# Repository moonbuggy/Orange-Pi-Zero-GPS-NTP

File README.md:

# Orange Pi Zero GPS NTP Server
An Orange Pi Zero with attached GPS, TFT and RTC devices, to create a stratum 1
NTP server.

<p><br/>
<em>Orange Pi Zero GPS NTP Server</em></p>

[moonbuggy/fbgpsclock][moonbuggy/fbgpsclock] is used to interface between the
display and the other devices.

*   [Hardware](#hardware)
    +   [Assembled](#assembled)
    +   [Components](#components)
        -   [Orange Pi Zero](#orange-pi-zero)
        -   [GPS (NEO-M8N)](#gps-neo-m8n)
        -   [TFT display (ST7789V driver)](#tft-display-st7789v-driver)
        -   [Real-time Clock (DS3231)](#real-time-clock-ds3231)
        -   [Power Switch](#power-switch)
    +   [Wiring](#wiring)
        -   [Schematic](#schematic)
        -   [Cable](#cable)
        -   [Power Splitter](#power-splitter)
*   [Software](#software)
    +   [Pre-built OS Image](#pre-built-os-image)
    +   [Manual Configuration](#manual-configuration)
        -   [Armbian](#armbian)
        -   [Status LED](#status-led)
        -   [gpsd](#gpsd)
        -   [chrony](#chrony)
        -   [fbgpsclock](#fbgpsclock)
*   [Links](#links)

## Hardware
### Assembled
<p><br/>
<em>internals</em></p>

<p><br/>
<em>internals (annotated)</em></p>

<p><br/>
<em>top</em></p>

<p><br/>
<em>rear</em></p>

<p><br/>
<em>side</em></p>

There's also [a gallery __(NSFW)__](https://imgur.com/a/yd1e8r0) with some
images from various stages of testing and building.

### Components
#### Orange Pi Zero
Although we're using an Orange Pi Zero (OPiZ) here, the specific single-board
computer used isn't all that important. Any device with UART, SPI, I2C and GPIO
interfaces should work, needing only one of each.

Any device tree overlays in this repository will, however, be specifically for
the OPiZ and would need to be modified for use on other SBCs.

#### GPS (NEO-M8N)
We're using a u-blox NEO-M8N GPS, although any GPS device that _gpsd_ can talk
to should work.

<p><br/>
<em>u-blox NEO-M8N module</em></p>

Soldering a wire to a point between the PPS LED and its current limiting
resistor provides a usable PPS signal on this module.

The GPS is attached through a UART interface (_UART2_), while the
PPS signal is connected separately through a GPIO pin (_pin 15_, _PA03_).

##### Bias tee
A bias tee is installed between the GPS module and the antenna. This allows us
to run the antenna's internal low-noise amplifier (LNA) off the 5V enclosure
supply, rather than the 3.3V that would be provided via the GPS module.Running
the LNA at a higher power should give us better signal.

##### Antenna
There's a lot of antenna options available, it really depends on the use case

A standard panel antenna seems to be more than adequate indoors, inside a
plastic enclosure with the rest of the hardware. Ideally the panel antenna
should have mounting holes so it can be screwed securely to the enclosure,
rather than being taped/glued to a circuit board as may be necessary with
antenna included with the GPS module.

#### TFT display (ST7789V driver)
An LCD screen attached to the OPiZ's SPI bus gives us a way to display
the current time and any other information that may be relevant.

<p><br/>
<em>2.0" SPI TFT</em></p>

A TFT with an ST7789V driver chip and 240x320 pixel resolution has been used in
this case, but a working device tree overlay for a 240x280 pixel display has
also been provided. Other resolutions will work with some minor modifications to
the DT overlay. Using a different driver chip is more complicated.

The exact dimensions of the display don't matter a great deal, it's really only
limited by how much surface area is available on the enclosure to fit a screen.

The TFT display is attached to the SPI1 bus.

#### Real-time Clock (DS3231)
A real-time clock provides accurate time immediately after booting. This is
useful because, coming from a cold start, the GPS module can take a little while
to establish a fix and begin providing time data. Covering this gap with an RTC
means we always have access to a time reference.

The DS3231 is a good option for a cheap and easy I2C RTC module.

<p><br/>
<em>DS3231 RTC module</em></p>

#### Power Switch
A power switch from [moonbuggy/GPIO-power-switch][moonbuggy/GPIO-power-switch]
lets us properly shutdown and cut power to the whole enclosure (including the GPS
module and bias tee).

Making use of the remaining free pins in the cable, we can use the following:

|    signal     | pin | GPIO |
|:-------------:|:---:|:----:|
| GPIO_POWEROFF | 21  | PA16 |
| KEY_POWER     | 12  | PA07 |
| READY_SIGNAL  | 16  | PA19 |

> [!NOTE]
> The _GPIO_SHUTDOWN_ signal requires `CONFIG_POWER_RESET_GPIO` and
> `CONFIG_POWER_RESET_GPIO_RESTART` to be enabled in the kernel, which may not
> be the case for a default OS install.

Due to pin 16 (_PA19_) having an internal pull-up resistor, we'll use the verson
of the power switch with the active low LED so the default LED state at power
up is _not-ready_.

More details are available at [moonbuggy/GPIO-power-switch][moonbuggy/GPIO-power-switch].

### Wiring
#### Schematic
<p><br/>
<em>GPIO wiring</em></p>

#### Cable
The specific pins chosen allow us to make a convenient cable to connect the GPS,
TFT and power control modules while leaving the I2C pins clear for the RTC
module to plug directly in.

<p><br/>
<em>GPS + 2.0" TFT + power control cable schematic</em></p>

> [!NOTE]
> The cable is wired for the specific attached devices. The OPiZ end is static,
> but the other connectors will need to be adjusted to match the pinout of the
> particular TFT and GPS modules in use.

Most of the connectors are standard pin sockets, with a 2x8 socket being used
for the OPiZ end 1x5 and 1x8 sockets on the GPS and TFT modules respectively.
A JST XH2.54 connector is used for the GPIO signals to/from the power control
board.

<p><br/>
<em>GPS + TFT + power control cable</em></p>

The OPiZ end of the cable will attach to GPIO pins 11 to 26. Using a
black wire for the ground connection to OPiZ pin 25 provides a convenient way to
align the connector, regardless of the other wire colours.

#### Power Splitter
<p><br/>
<em>power splitter</em></p>

In an ideal world there'd be enough room in the enclosure to combine this
splitter and the power control circuit on a single PCB, to save a cable run
(although it's not a big deal that they're separate).

Closing the jumper bypasses the switch in the power control circuit, directly
connecting the OPiZ and bias tee to ground, and is useful during testing. The
button and LED in the power control circuit will still work as expected, and
the MOSFET will still switch, it just won't have any effect and actually cut
power after a <code>shutdown -h</code> command or button press.

## Software
### Pre-built OS Image
There's a pre-built Armbian image in the
[releases](https://github.com/moonbuggy/Orange-Pi-Zero-GPS-NTP/releases/latest)
which will work out of the box for a build using the same (or compatible)
hardware wired as described above. All the setup and configuration steps below
have been done during the image creation.

Simply write the _*.img.xz_ file to an SD card, put the card in the OPiZ, power
it up.

GPS devices other than the Neo M8N should work easily with this image, so long
as they use _uart2_ (and use _pin 15_/_PA03_ for the PPS signal). A different
display controller or RTC, however, would be incompatible with the device tree
in the image.

It's possible to re-configure the pre-built OS after first boot, if necessary
to adjust for differing hardware. Depending on how much modification is needed,
it may be easier to start with a bare OS and do the manual steps described
below.

#### Packages
The _*.deb_ files in the release are packages which can be installed on top of
an existing Armbian install, as an alternative to the pre-built image.

These packages just add the modules necessary for the GPIO power switch to work
to the kernel. They do not install any GPS/NTP/TFT software or handle any of the
configuration like the image does.

Install with: <code>sudo dpkg -i *.deb</code>

### Manual Configuration
#### Armbian
We need to enable the _i2c0_, _pps-gpio_, _tve_ and _uart2_ devices. It probably
makes sense to enable _clock-1.2GHz-1.3v_ as well, if it isn't by default. This
can be done in `armbian-config` or by editing _/boot/armbianEnv.txt_.

A parameter for the PPS pin needs to be defined in _/boot/armbianEnv.txt_,
regardless of how the hardware overlays above are enabled:
```sh
sudo sh -c "echo 'param_pps_pin=PA3' >> /boot/armbianEnv.txt"
```

##### Custom Device Tree Overlays
The device tree source (DTS) files in this repo for the display are for an
ST7789V SPI TFT controller with a 240x280 or 240x320 display. They can be
modified for other resolutions.

The most relevant areas, if we're modifying these DTS files for a different
display, are `opiz_display_pins` and the width, height and _0x1000037_ values
in `opizdisplay`.

The RTC DTS is for a DS3231N connected to _i2c0_ (pins 3 and 5).

The _gpio-key-power.dts_ overlay allows a physical button to turn the SBC on
(by pulling pin 12/PA07 low), and the _sun8i-h3-gpio-poweroff.dts_ overlay
allows the OS to signal it has shutdown (by pulling pin 21/PA16 high).

To install, pick the appropriate DTS for the display, then:
```sh
sudo armbian-add-overlay st7789v-<res>.dts
sudo armbian-add-overlay rtc-ds3231n.dts
sudo armbian-add-overlay gpio-key-power.dts
sudo armbian-add-overlay sun8i-h3-gpio-poweroff.dts
```

###### Display Driver Init
Both DTS files contain a custom init for the driver. This init sequence is based
off that in the kernel driver (as opposed to that in the ST7789V datasheet,
which differs in some places), with only the _VSCSAD (37h): Vertical Scroll
Start Address of RAM_ register being changed (and then only for the _240x280_
DTS).

The _VSCSAD (37h)_ register basically aligns the display area. Since the driver
chip will support up to 240x320, for a lower resolution screen we need to make
sure the pixels the driver is mapping to are in the visible portion.

i.e. for a 280px high screen, there's 40px of dead space. _VSCSAD (37h)_ lets us
scroll the vertical alignment up or down if that dead space is being displayed
as a black area at the top or bottom of the screen.

In the _240x280_ DTS file we're moving 300px, because we've got 20px dead
space top and bottom. Moving just 20px moves in the wrong direction. Converting
300 to hex gives us 012C, which then looks like this in the DTS: `0x1000037 0x01
0x2c`

The _240x320_ DTS is just using the kernel driver's default init unmodified. The
`init` section probably doesn't need to be in this DTS, but it's a convenient
reference for the defaults.

#### Status LED
If using the [moonbuggy/GPIO-power-switch][moonbuggy/GPIO-power-switch] module,
the status LED can be changed from red to green to indicate the device is ready
by pulling pin 16 (_PA19_) low. In this case we'll indicate 'ready' with a
systemd service, once both the _gpsd_ and _chrony_ services are running.

###### /usr/lib/systemd/system/ready.target
```ini
[Unit]
Description=System is booted and ready (for toggling status LED)
Requires=fbgpsclock.service chrony.service gpsd.service gpsd.socket multi-user.target
After=fbgpsclock.service chrony.service gpsd.service gpsd.socket multi-user.target
AllowIsolate=yes
```

###### /usr/lib/systemd/system/ready-led.service
```ini
[Unit]
Description='ready' status indicator LED
After=fbgpsclock.service chrony.service gpsd.service gpsd.socket
Requires=fbgpsclock.service chrony.service gpsd.service gpsd.socket

[Service]
Type=oneshot
ExecStart=gpioset 0 19=0
ExecStop=gpioset 0 19=1
RemainAfterExit=yes

[Install]
WantedBy=ready.target
```

To enable the service:
```sh
sudo systemctl daemon-reload
sudo systemctl enable ready-led
sudo systemctl set-default ready.target
```

#### gpsd
##### Installation
```sh
sudo apt install gpsd setserial

# optional tools
sudo apt install gpsd-tools pps-tools
```

###### /etc/default/gpsd
```ini
# Devices gpsd should connect to at boot time.
# They need to be read/writeable, either by user gpsd or the group dialout.
DEVICES="/dev/ttyS2 /dev/pps0"

# Other options you want to pass to gpsd
GPSD_OPTIONS="-n -s 115200"

# Automatically hot add/remove USB GPS devices via gpsdctl
USBAUTO="true"

/bin/stty -F /dev/ttyS2 115200
/bin/setserial /dev/ttyS2 low_latency
```

The GPS device may need to be configured to run at 115200bps, with commands
appropriate for the particular device. Alternatively, the serial port could be
run at a slower speed, but I found my _u-blox NEO M8N_ defaulted to 9600bps
and this was slow enough to generate complaints in logs about missing data.

Once configured:
```sh
sudo systemctl daemon-reload
sudo systemctl enable gpsd
sudo systemctl start gpsd
```

#### chrony
##### Installation
```sh
sudo apt install chrony
```

There's a few ways Chrony can talk to gpsd. The shared memory (SHM) method
requires _Chrony_ to poll for updates, the socket driver (SOCK) doesn't require
_Chrony_ to poll and on paper should have less overhead. The socket driver
should also be more accurate than the PPS driver.

Using SOCK for the GPS signal requires gpsd >=3.25, and SOCK generally requires
_gpsd_ to be started after _Chrony_. Only one GPS and one PPS source needs to be
enabled.

###### /etc/chrony/conf.d/gpsd.conf
```ini
# using shared memory
refclock SHM 0 refid GPS offset 0.200 trust

# using PPS driver
#refclock PPS /dev/pps0 refid PPS lock GPS require

# using socket driver
#refclock SOCK /run/chrony.ttyS2.sock refid GPS offset 0.200 trust  # requires gpsd >=3.25
refclock SOCK /run/chrony.pps0.sock refid PPS precision 1e-7 require
```

The offset value is estimated from `gpsmon -n`, and should be set to something
appropriate for any individual setup as it will vary. It makes sense to do a
proper calibration based on a period of GPS data collection, rather than just an
the instantaneous estimate from real-time monitoring.

The default configuration for the RTC is for chrony to tell the system to set it
every 11 minutes. To let chrony set the time from the RTC (as a backup if
there's some issue with the GPS), it needs to be run with the `-s` argument.

To ensure only the GPS and PPS signals are used, the default
`/etc/chrony/chrony.conf` file be be edited to comment out the sources it
provides.

###### /etc/default/chrony
```sh
# This is a configuration file for /etc/init.d/chrony and
# /lib/systemd/system/chrony.service; it allows you to pass various options to
# the chrony daemon without editing the init script or service file.

# Options to pass to chrony.
DAEMON_OPTS="-F 1 -r -m -s"
```

The DS3231 RTC will only continue counting time on battery if the
E̅O̅S̅C̅ and OSF bits in the register
are clear. Assuming the DS3231 is at 0x68 on bus 0:

```sh
# E̅O̅S̅C̅
i2cset -y 0 0x68 0x0e 0x1c

# OSF
i2cset -y 0 0x68 0x0f 0x08
```

#### fbgpsclock
The [fbgpsclock][moonbuggy/fbgpsclock] repo contains software for displaying
time and GPS information on the TFT display.

<p><br/>
<em>fbgpsclock screenshot</em></p>

##### Installation
Check build dependencies are installed (this may not be a complete dependency
list):
```sh
sudo apt install gcc libgps-dev make
```

Then build and install:
```sh
git clone --depth=1 https://github.com/moonbuggy/fbgpsclock.git
cd fbgpsclock/
make
sudo make install
sudo systemctl enable fbgpsclock
sudo systemctl start fbgpsclock
```

More detail and configuration information is available at [moonbuggy/fbgpsclock][moonbuggy/fbgpsclock].

## Links
### Software
*   [moonbuggy/fbgpsclock][moonbuggy/fbgpsclock]
*   [moonbuggy/sbc-os-images][moonbuggy/sbc-os-images]

### Hardware
*   [moonbuggy/GPIO-power-switch][moonbuggy/GPIO-power-switch]

### Datasheets
*   [DS3231](https://www.analog.com/media/en/technical-documentation/data-sheets/DS3231.pdf)
*   [NEO-M8N](https://content.u-blox.com/sites/default/files/NEO-M8-FW3_DataSheet_UBX-15031086.pdf)
*   [ST7789V](https://newhavendisplay.com/content/datasheets/ST7789V.pdf)

[moonbuggy/fbgpsclock]: https://github.com/moonbuggy/fbgpsclock
[moonbuggy/sbc-os-images]: https://github.com/moonbuggy/sbc-os-images
[moonbuggy/GPIO-power-switch]: https://github.com/moonbuggy/GPIO-power-switch

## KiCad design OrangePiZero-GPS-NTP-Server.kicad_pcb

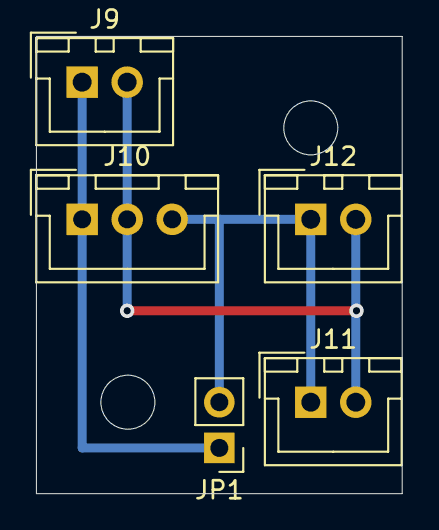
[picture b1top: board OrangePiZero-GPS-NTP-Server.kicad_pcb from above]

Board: 2 copper layers, 20.3 x 25.4 mm, 5 parts (0 on the bottom side), 3 nets.

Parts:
J9: Vin; JST_XH_B02B-XH-A_02x2.50mm_Straight
J10: Power Switch; JST_XH_B03B-XH-A_03x2.50mm_Straight
J11: GPS; JST_XH_B02B-XH-A_02x2.50mm_Straight
J12: Bias Tee; JST_XH_B02B-XH-A_02x2.50mm_Straight
JP1: Jumper_2_Open; Pin_Header_Straight_1x02_Pitch2.54mm

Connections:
+5V: J9.2, J10.2, J11.2, J12.2
/Power Distribution Board/GND_SWITCHED: J10.3, J11.1, J12.1, JP1.2
GND: J9.1, J10.1, JP1.1

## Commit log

2024-02-21 added power button
2024-02-21 added pre-built Armbian image
2024-04-18 fixed typo
2024-07-13 added DS3231 i2cset commands
2025-03-06 added example for gpsd socket driver
